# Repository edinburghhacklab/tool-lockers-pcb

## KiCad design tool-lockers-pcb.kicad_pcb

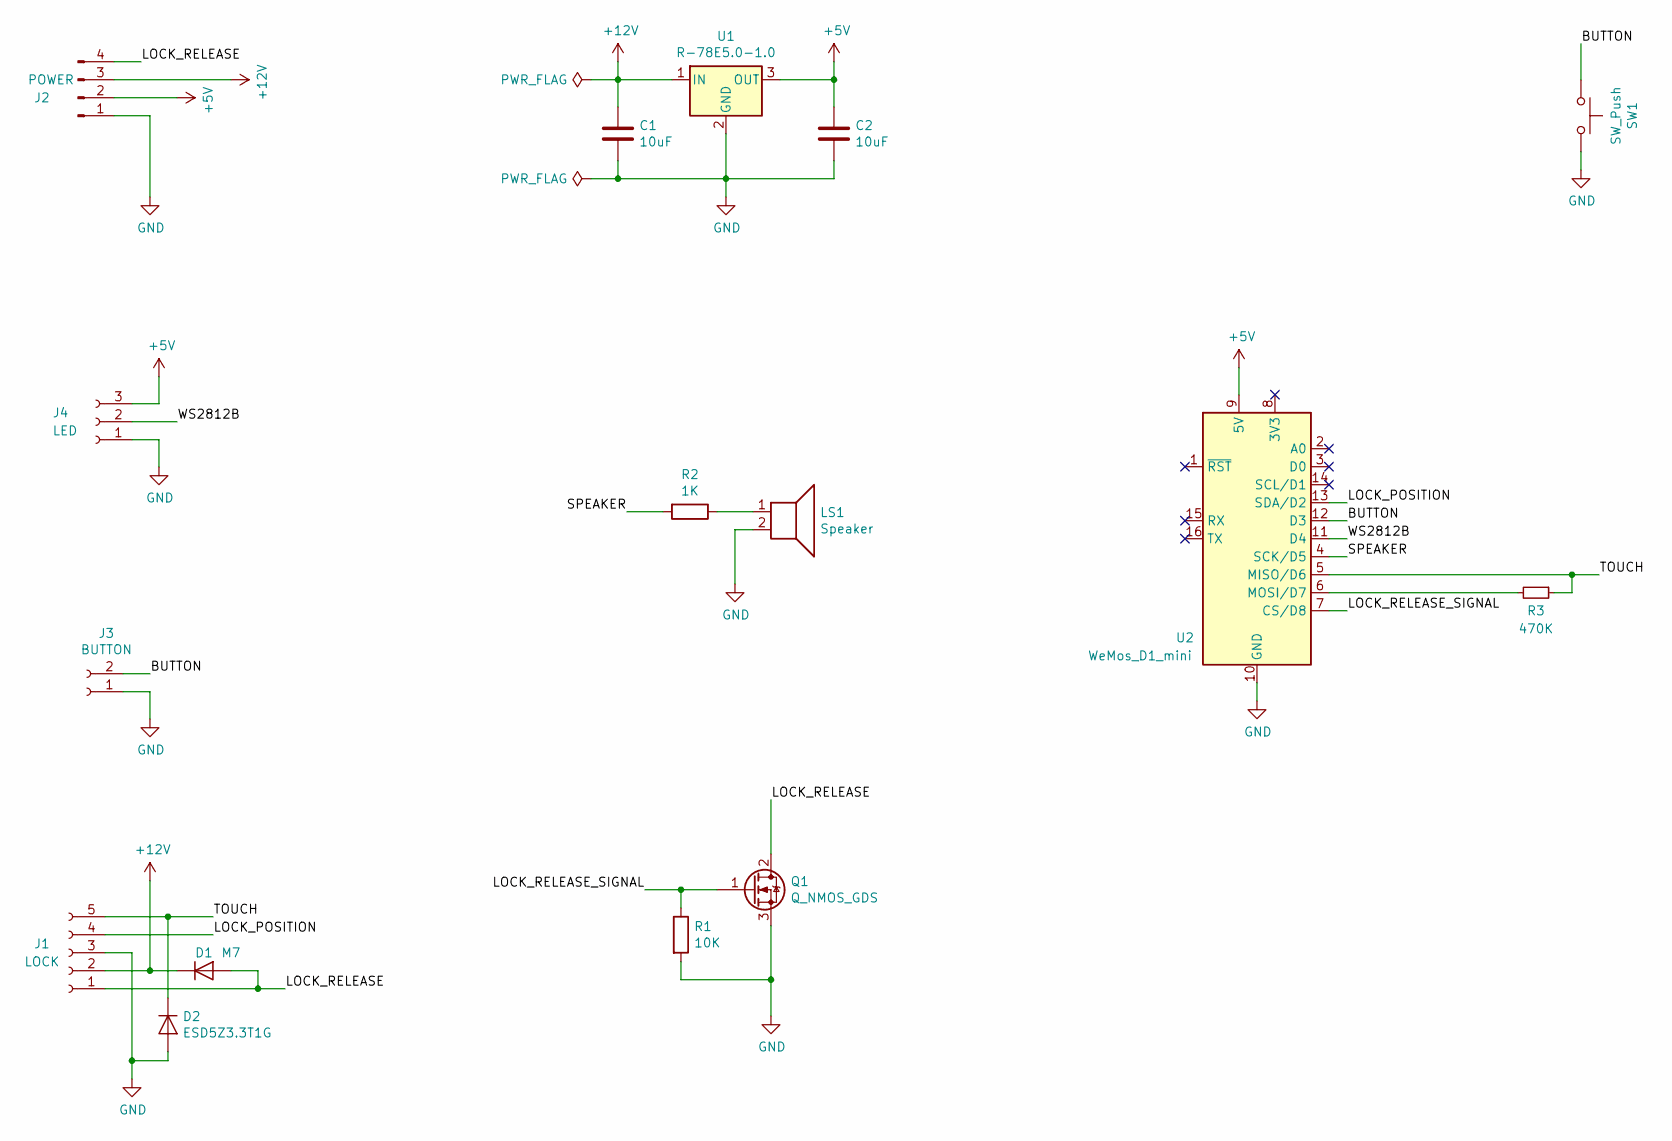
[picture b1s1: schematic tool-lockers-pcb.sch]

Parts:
C1, C2: 10uF; C_0805_2012Metric
D1: M7; D_SMA
D2: ESD5Z3.3T1G; D_SOD-523
J1: LOCK; PhoenixContact_MC_1,5_5-G-3.81_1x05_P3.81mm_Horizontal
J2: POWER; PhoenixContact_MC_1,5_4-G-3.81_1x04_P3.81mm_Horizontal
J3: BUTTON; PhoenixContact_MC_1,5_2-G-3.81_1x02_P3.81mm_Horizontal
J4: LED; PhoenixContact_MC_1,5_3-G-3.81_1x03_P3.81mm_Horizontal
LS1: Speaker; Buzzer_12x9.5RM7.6
Q1: Q_NMOS_GDS; TO-252-3_TabPin2
R1: 10K; R_0603_1608Metric
R2: 1K; R_0603_1608Metric
R3: 470K; R_0603_1608Metric
SW1: SW_Push; CK_D6_PUSH_BUTTON
U1: R-78E5.0-1.0; Converter_DCDC_RECOM_R-78E-0.5_THT
U2: WeMos_D1_mini; WEMOS_D1_mini_light

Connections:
+5V: C2.1, J2.2, J4.3, U1.3 (OUT), U2.9 (5V)
+12V: C1.1, D1.1 (K), J1.2, J2.3, U1.1 (IN)
/BUTTON: J3.2, SW1.1, U2.12 (D3)
/LOCK_POSITION: J1.4, U2.13 (SDA/D2)
/LOCK_RELEASE: D1.2 (A), J1.1, J2.4, Q1.2 (D)
/LOCK_RELEASE_SIGNAL: Q1.1 (G), R1.1, U2.7 (CS/D8)
/SPEAKER: R2.2, U2.4 (SCK/D5)
/TOUCH: D2.1 (K), J1.5, R3.1, U2.5 (MISO/D6)
/WS2812B: J4.2, U2.11 (D4)
GND: C1.2, C2.2, D2.2 (A), J1.3, J2.1, J3.1, J4.1, LS1.2, Q1.3 (S), R1.2, SW1.2, U1.2 (GND), U2.10 (GND)
unnamed: LS1.1, R2.1
unnamed: R3.2, U2.6 (MOSI/D7)

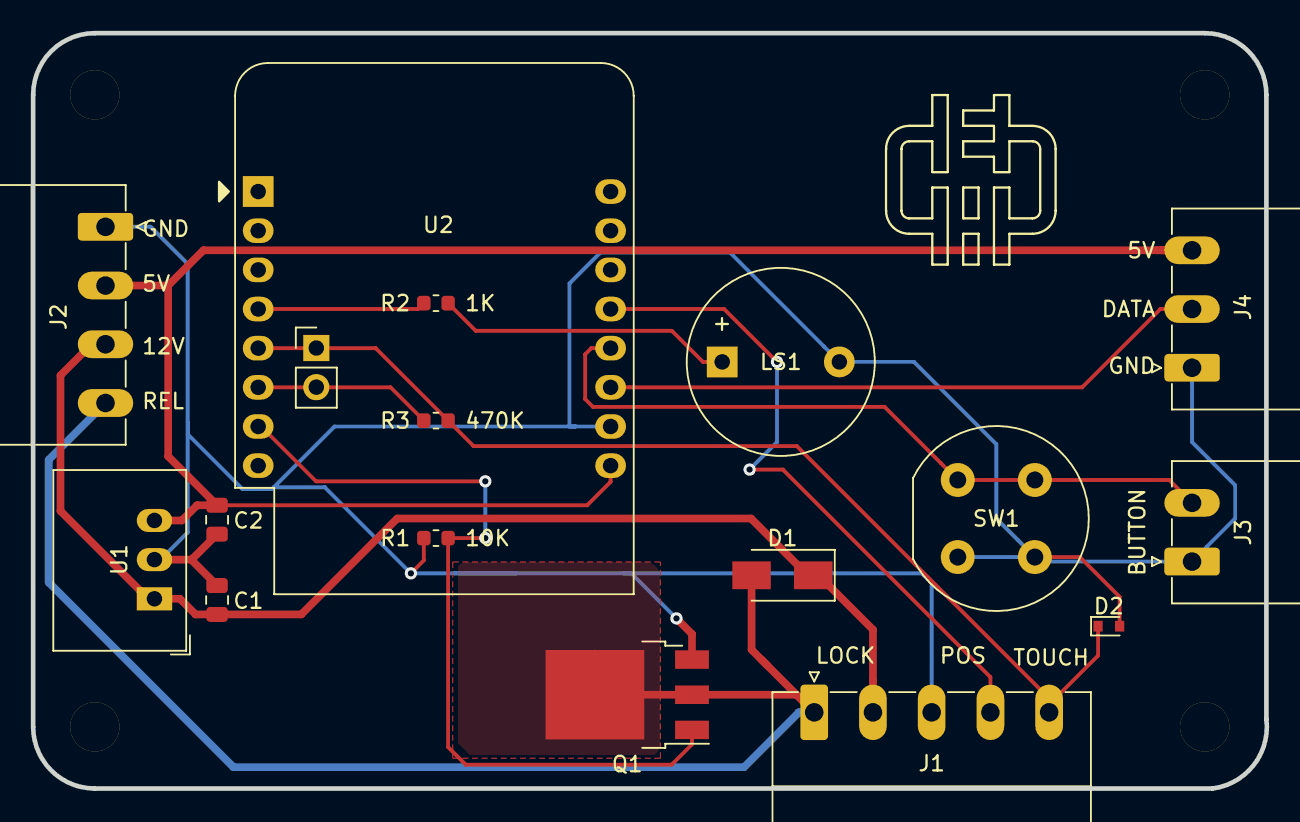
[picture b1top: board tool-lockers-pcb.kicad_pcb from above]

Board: 2 copper layers, 80.0 x 49.0 mm, 17 parts (0 on the bottom side), 12 nets.

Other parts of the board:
DP7043: DP8049

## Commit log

2019-07-26 Fix MOSFET footprint and add thermal zone
